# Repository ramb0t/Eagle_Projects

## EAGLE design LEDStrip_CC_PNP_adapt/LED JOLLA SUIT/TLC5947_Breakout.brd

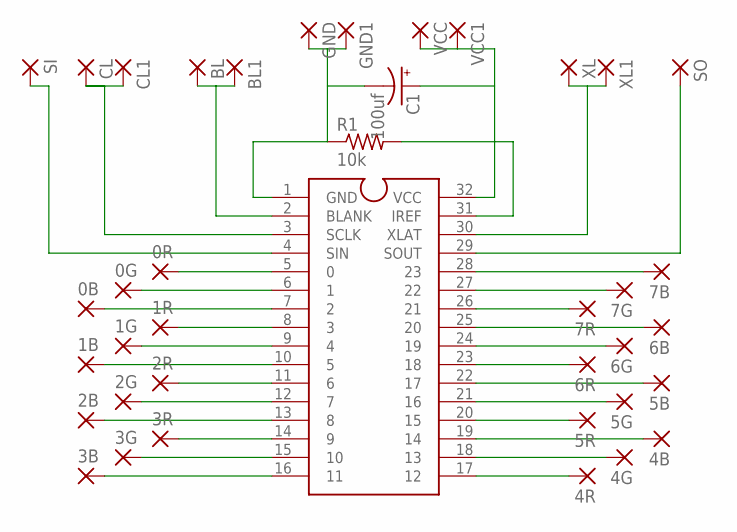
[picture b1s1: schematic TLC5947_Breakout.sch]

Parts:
0B, 0G, 0R, 1B, 1G, 1R, 2B, 2G, 2R, 3B, 3G, 3R, 4B, 4G, 4R, 5B, 5G, 5R, 6B, 6G, 6R, 7B, 7G, 7R: SMD2; SMD1,27-2,54
BL, BL1: SMD2; SMD1,27-2,54
C1: 100uf; E2,5-6
CL, CL1: SMD2; SMD1,27-2,54
GND, GND1: SMD2; SMD1,27-2,54
R1: 10k; 0207/10
SI: SMD2; SMD1,27-2,54
SO: SMD2; SMD1,27-2,54
U$1: TLC5947DAC; DAP38
VCC, VCC1: SMD2; SMD1,27-2,54
XL, XL1: SMD2; SMD1,27-2,54

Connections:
GND: C1.-, GND.1, GND1.1, R1.1, U$1.1 (GND)
unnamed: R1.2, U$1.31 (IREF)
unnamed: U$1.30 (XLAT), XL.1, XL1.1
unnamed: 0R.1, U$1.5 (0)
unnamed: 0G.1, U$1.6 (1)
unnamed: 0B.1, U$1.7 (2)
unnamed: 1R.1, U$1.8 (3)
unnamed: 1G.1, U$1.9 (4)
unnamed: 1B.1, U$1.10 (5)
unnamed: 2R.1, U$1.11 (6)
unnamed: 2G.1, U$1.12 (7)
unnamed: 2B.1, U$1.13 (8)
unnamed: 3R.1, U$1.14 (9)
unnamed: 3G.1, U$1.15 (10)
unnamed: 3B.1, U$1.16 (11)
unnamed: 4R.1, U$1.17 (12)
unnamed: 4G.1, U$1.18 (13)
unnamed: 4B.1, U$1.19 (14)
unnamed: 5R.1, U$1.20 (15)
unnamed: 5G.1, U$1.21 (16)
unnamed: 5B.1, U$1.22 (17)
unnamed: 6R.1, U$1.23 (18)
unnamed: 6G.1, U$1.24 (19)
unnamed: 6B.1, U$1.25 (20)
unnamed: 7R.1, U$1.26 (21)
unnamed: 7G.1, U$1.27 (22)
unnamed: 7B.1, U$1.28 (23)
unnamed: SI.1, U$1.4 (SIN)
unnamed: SO.1, U$1.29 (SOUT)
unnamed: CL.1, CL1.1, U$1.3 (SCLK)
unnamed: BL.1, BL1.1, U$1.2 (BLANK)
VCC: C1.+, U$1.32 (VCC), VCC.1, VCC1.1

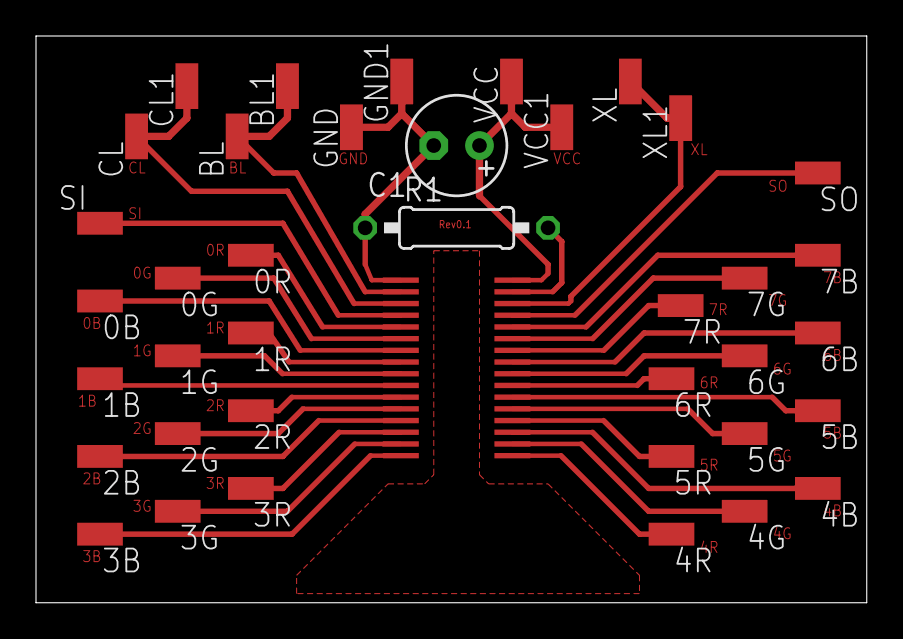
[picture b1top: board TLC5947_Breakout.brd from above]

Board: 2 copper layers, 46.2 x 31.5 mm, 39 parts (0 on the bottom side), 32 nets.

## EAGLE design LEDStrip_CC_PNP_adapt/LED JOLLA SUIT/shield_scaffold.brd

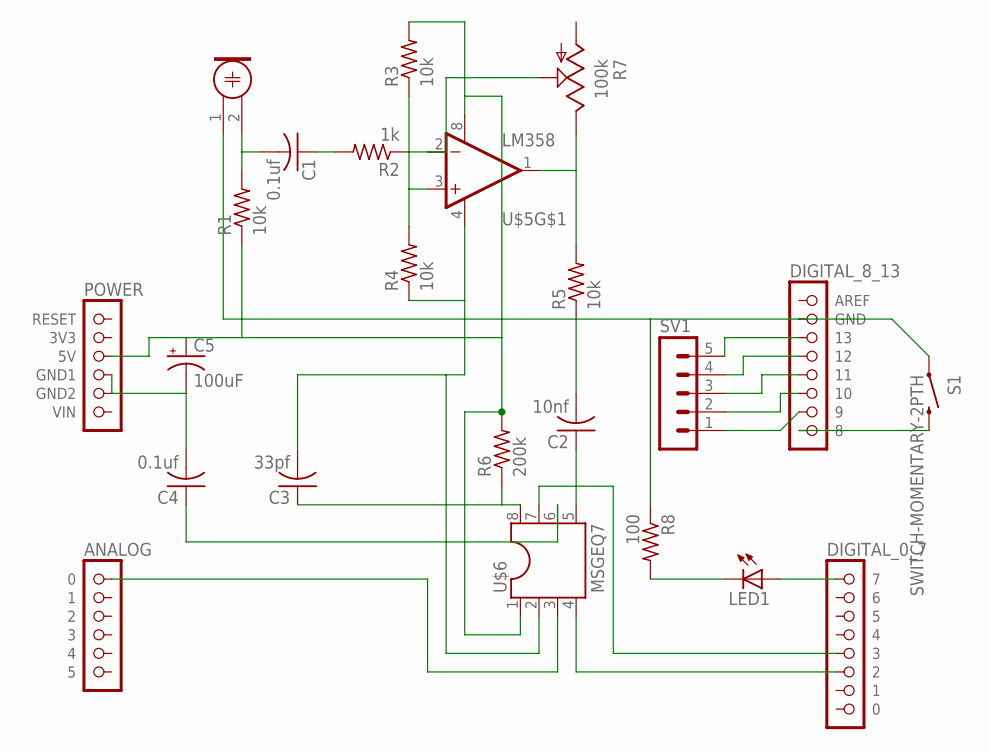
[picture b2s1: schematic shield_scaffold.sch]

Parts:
C1, C4: 0.1uf; C050-030X075
C2: 10nf; C050-030X075
C3: 33pf; C050-030X075
C5: 100uF; E3,5-8
LED1: LED3MM
M1: ELECTRET_MICROPHON-F6050AP; F6050AP
R1, R3, R4, R5: 10k; 0207/10
R2: 1k; 0207/10
R6: 200k; 0207/10
R7: 100k; PT-10
R8: 100; 0207/10
S1: SWITCH-MOMENTARY-2PTH; TACTILE-PTH
SV1: MA05-1
U$1: POWER; 1X06
U$2: ANALOG; 1X06
U$3: DIGITAL_0_7; 1X08
U$4: DIGITAL_8_13; 1X08
U$5: LM358; DIP08
U$6: MSGEQ7; SOCKET-08

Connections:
GND: C3.2, M1.1, R4.1, R8.1, S1.1, U$4.2 (GND), U$5.4 (V-), U$6.2
unnamed: C1.2, M1.2, R1.2
unnamed: C1.1, R2.2
unnamed: C4.1, U$6.6
unnamed: R2.1, R7.S, U$5.2 (-IN)
unnamed: S1.3 (2), U$4.8
unnamed: R3.1, R4.2, U$5.3 (+IN)
unnamed: R5.2, R7.E, U$5.1 (OUT)
unnamed: C2.2, R5.1
unnamed: C2.1, U$6.5
unnamed: LED1.A, U$3.1 (7)
unnamed: SV1.5, U$4.3 (13)
unnamed: U$2.1 (0), U$6.3
unnamed: U$3.6 (2), U$6.4
unnamed: C3.1, R6.1, U$6.8
unnamed: U$3.5 (3), U$6.7
unnamed: SV1.4, U$4.4 (12)
unnamed: SV1.3, U$4.5 (11)
unnamed: SV1.2, U$4.6 (10)
unnamed: SV1.1, U$4.7 (9)
unnamed: LED1.K (C), R8.2
unnamed: C4.2, C5.-, U$1.4 (GND1), U$1.5 (GND2)
unnamed: C5.+, R1.1, R3.2, R6.2, U$1.3 (5V), U$5.8 (V+), U$6.1

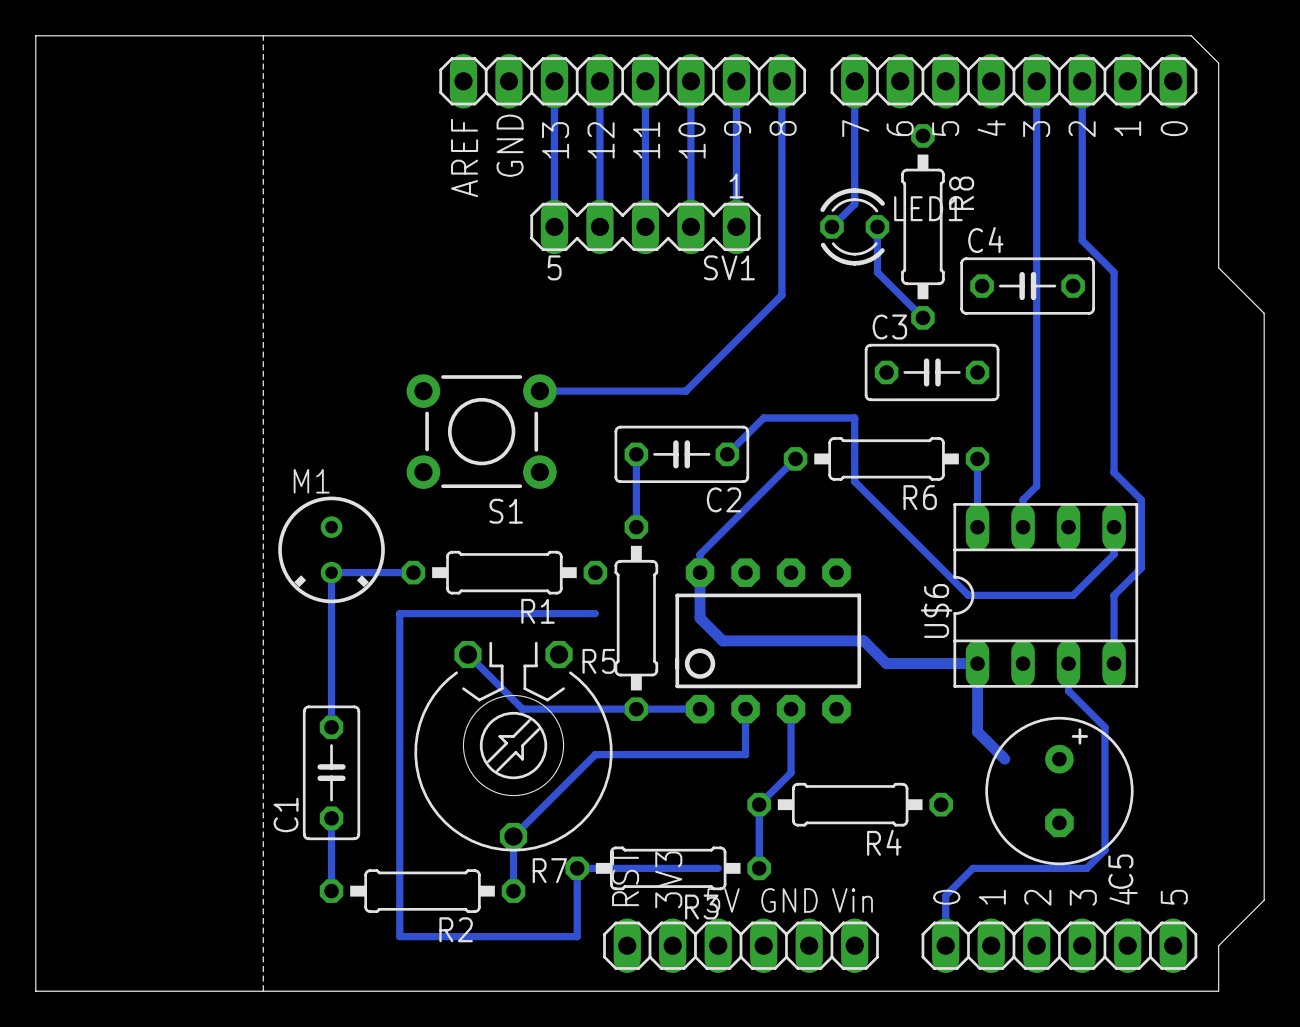
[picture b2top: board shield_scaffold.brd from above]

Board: 2 copper layers, 68.6 x 53.3 mm, 23 parts (0 on the bottom side), 23 nets.

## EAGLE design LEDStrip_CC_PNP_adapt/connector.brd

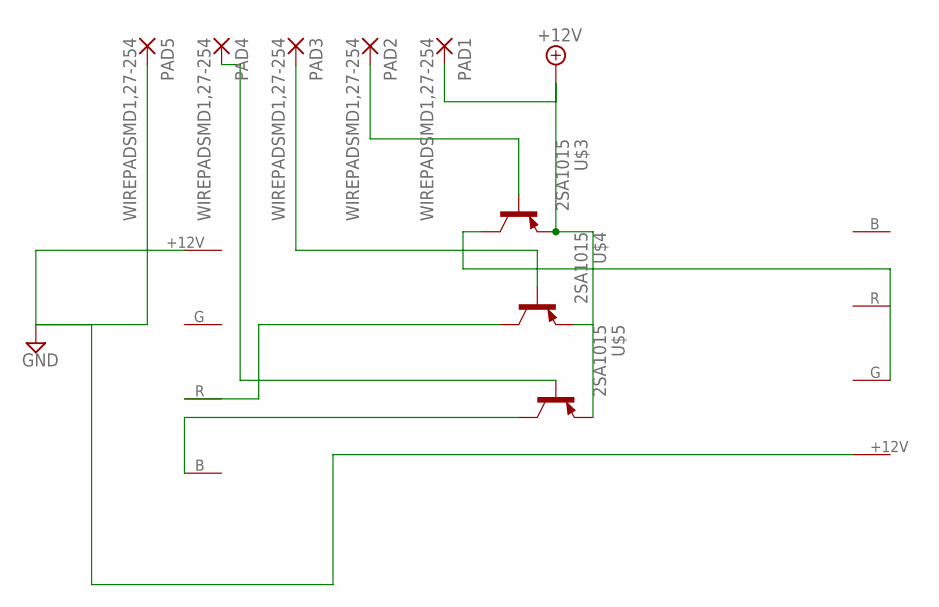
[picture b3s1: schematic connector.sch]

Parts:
PAD1, PAD2, PAD3, PAD4, PAD5: WIREPADSMD1,27-254; SMD1,27-2,54
U$1, U$2: LED_STRIP_SOLDER_PAD; STRIP
U$3, U$4, U$5: 2SA1015; TO92-EBC

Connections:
+12V: PAD1.1, U$3.E, U$4.E, U$5.E
GND: PAD5.1, U$2.+12V
unnamed: U$2.B, U$5.C
unnamed: U$2.R, U$4.C
unnamed: U$1.G, U$3.C
unnamed: PAD2.1, U$3.B
unnamed: PAD3.1, U$4.B
unnamed: PAD4.1, U$5.B

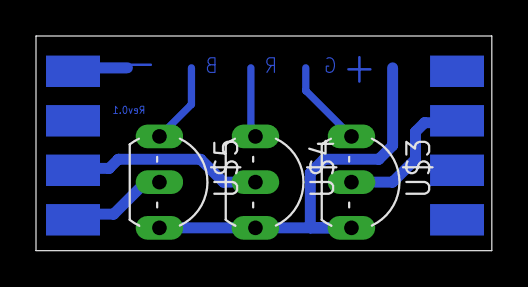
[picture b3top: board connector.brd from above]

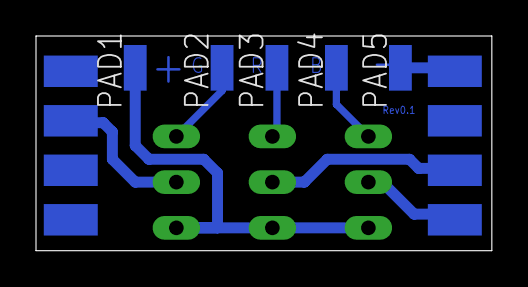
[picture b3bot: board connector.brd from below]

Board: 2 copper layers, 25.3 x 11.9 mm, 10 parts (7 on the bottom side), 8 nets.

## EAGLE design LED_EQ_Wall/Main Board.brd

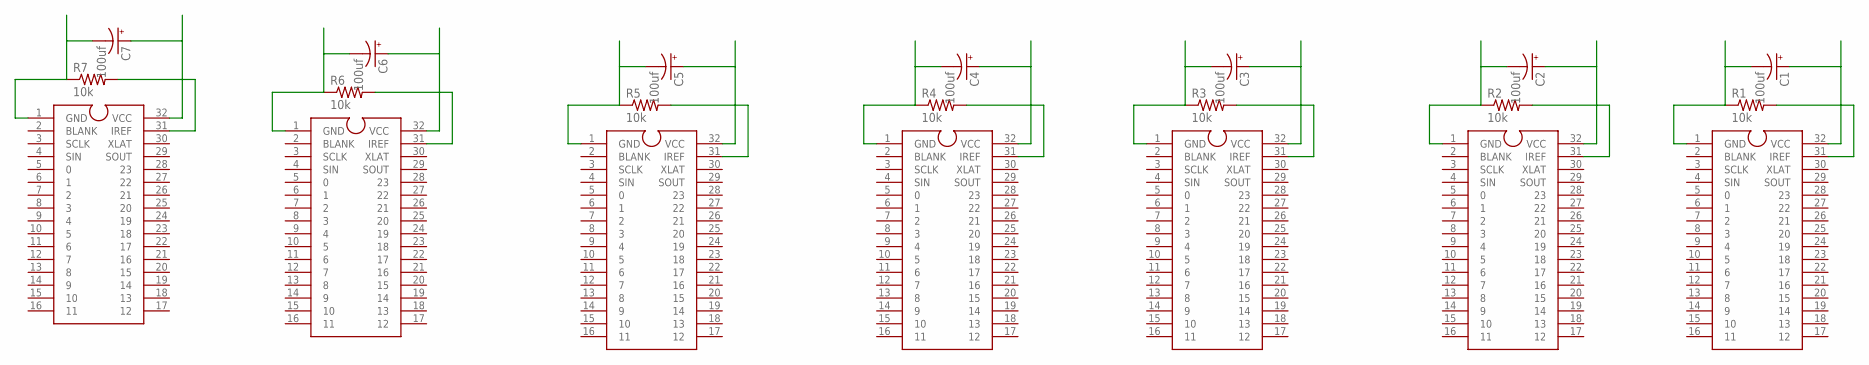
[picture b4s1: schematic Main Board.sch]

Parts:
C1, C2, C3, C4, C5, C6, C7: 100uf; E2,5-6
R1, R2, R3, R4, R5, R6, R7: 10k; 0207/10
U$1, U$2, U$3, U$4, U$5, U$6, U$7: TLC5947DAC; DAP38

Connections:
GND: C1.-, R1.1, U$1.1 (GND)
GND1: C2.-, R2.1, U$2.1 (GND)
GND2: C3.-, R3.1, U$3.1 (GND)
GND3: C4.-, R4.1, U$4.1 (GND)
GND4: C5.-, R5.1, U$5.1 (GND)
GND5: C6.-, R6.1, U$6.1 (GND)
GND6: C7.-, R7.1, U$7.1 (GND)
unnamed: R1.2, U$1.31 (IREF)
unnamed: R2.2, U$2.31 (IREF)
unnamed: R3.2, U$3.31 (IREF)
unnamed: R4.2, U$4.31 (IREF)
unnamed: R5.2, U$5.31 (IREF)
unnamed: R6.2, U$6.31 (IREF)
unnamed: R7.2, U$7.31 (IREF)
VCC: C1.+, U$1.32 (VCC)
VCC1: C2.+, U$2.32 (VCC)
VCC2: C3.+, U$3.32 (VCC)
VCC3: C4.+, U$4.32 (VCC)
VCC4: C5.+, U$5.32 (VCC)
VCC5: C6.+, U$6.32 (VCC)
VCC6: C7.+, U$7.32 (VCC)

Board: 2 copper layers, 21 parts (0 on the bottom side), 21 nets, no tracks yet.

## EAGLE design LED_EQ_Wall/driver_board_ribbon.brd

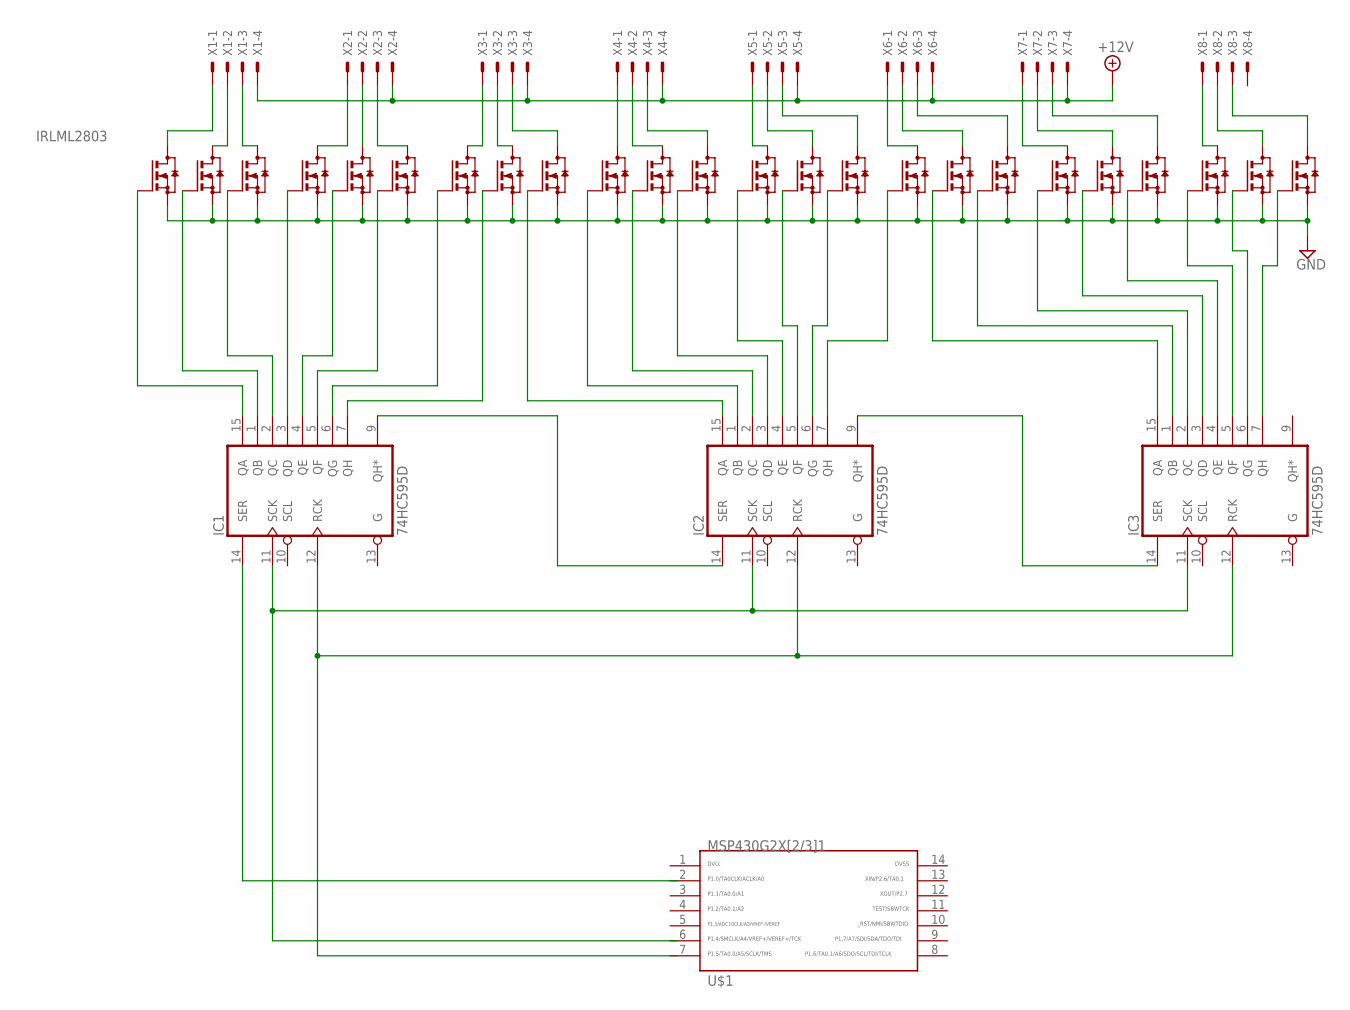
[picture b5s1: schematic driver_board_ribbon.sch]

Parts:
IC1, IC2, IC3: 74HC595D; SO16
U$1: G2X[2/3]1---PW14; PW14
U$3, U$4, U$5, U$6, U$7, U$8, U$9, U$10, U$11, U$12, U$13, U$14, U$15, U$16, U$17, U$18, U$19, U$20, U$21, U$22, U$23, U$24, U$25, U$26: IRLML2803; SOT23
X1, X2, X3, X4, X5, X6, X7, X8: KK-156-4

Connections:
+12V: X1.4, X2.4, X3.4, X4.4, X5.4, X6.4, X7.4
GND: IC1.8 (GND), IC2.8 (GND), IC3.8 (GND), U$3.2 (S), U$4.2 (S), U$5.2 (S), U$6.2 (S), U$7.2 (S), U$8.2 (S), U$9.2 (S), U$10.2 (S), U$11.2 (S), U$12.2 (S), U$13.2 (S), U$14.2 (S), U$15.2 (S), U$16.2 (S), U$17.2 (S), U$18.2 (S), U$19.2 (S), U$20.2 (S), U$21.2 (S), U$22.2 (S), U$23.2 (S), U$24.2 (S), U$25.2 (S), U$26.2 (S)
unnamed: IC1.9 (QH*), IC2.14 (SER)
unnamed: IC2.9 (QH*), IC3.14 (SER)
unnamed: IC1.11 (SCK), IC2.11 (SCK), IC3.11 (SCK)
unnamed: IC1.12 (RCK), IC2.12 (RCK), IC3.12 (RCK)
unnamed: U$3.3 (D), X1.1
unnamed: U$4.3 (D), X1.2
unnamed: U$5.3 (D), X1.3
unnamed: U$6.3 (D), X2.1
unnamed: U$7.3 (D), X2.2
unnamed: U$8.3 (D), X2.3
unnamed: U$9.3 (D), X3.1
unnamed: U$10.3 (D), X3.2
unnamed: U$11.3 (D), X3.3
unnamed: U$12.3 (D), X4.1
unnamed: U$13.3 (D), X4.2
unnamed: U$14.3 (D), X4.3
unnamed: U$15.3 (D), X5.1
unnamed: U$16.3 (D), X5.2
unnamed: U$17.3 (D), X5.3
unnamed: U$18.3 (D), X6.1
unnamed: U$19.3 (D), X6.2
unnamed: U$20.3 (D), X6.3
unnamed: U$21.3 (D), X7.1
unnamed: U$22.3 (D), X7.2
unnamed: U$23.3 (D), X7.3
unnamed: U$24.3 (D), X8.1
unnamed: U$25.3 (D), X8.2
unnamed: U$26.3 (D), X8.3
unnamed: IC1.7 (QH), U$10.1 (G)
unnamed: IC1.6 (QG), U$9.1 (G)
unnamed: IC1.5 (QF), U$8.1 (G)
unnamed: IC1.4 (QE), U$7.1 (G)
unnamed: IC1.3 (QD), U$6.1 (G)
unnamed: IC1.2 (QC), U$5.1 (G)
unnamed: IC1.1 (QB), U$4.1 (G)
unnamed: IC1.15 (QA), U$3.1 (G)
unnamed: IC2.15 (QA), U$11.1 (G)
unnamed: IC2.1 (QB), U$12.1 (G)
unnamed: IC2.2 (QC), U$13.1 (G)
unnamed: IC2.3 (QD), U$14.1 (G)
unnamed: IC2.4 (QE), U$15.1 (G)
unnamed: IC2.5 (QF), U$16.1 (G)
unnamed: IC2.6 (QG), U$17.1 (G)
unnamed: IC2.7 (QH), U$18.1 (G)
unnamed: IC3.15 (QA), U$19.1 (G)
unnamed: IC3.1 (QB), U$20.1 (G)
unnamed: IC3.2 (QC), U$21.1 (G)
unnamed: IC3.3 (QD), U$22.1 (G)
unnamed: IC3.4 (QE), U$23.1 (G)
unnamed: IC3.5 (QF), U$24.1 (G)
unnamed: IC3.6 (QG), U$25.1 (G)
unnamed: IC3.7 (QH), U$26.1 (G)
VCC: IC1.16 (VCC), IC2.16 (VCC), IC3.16 (VCC)

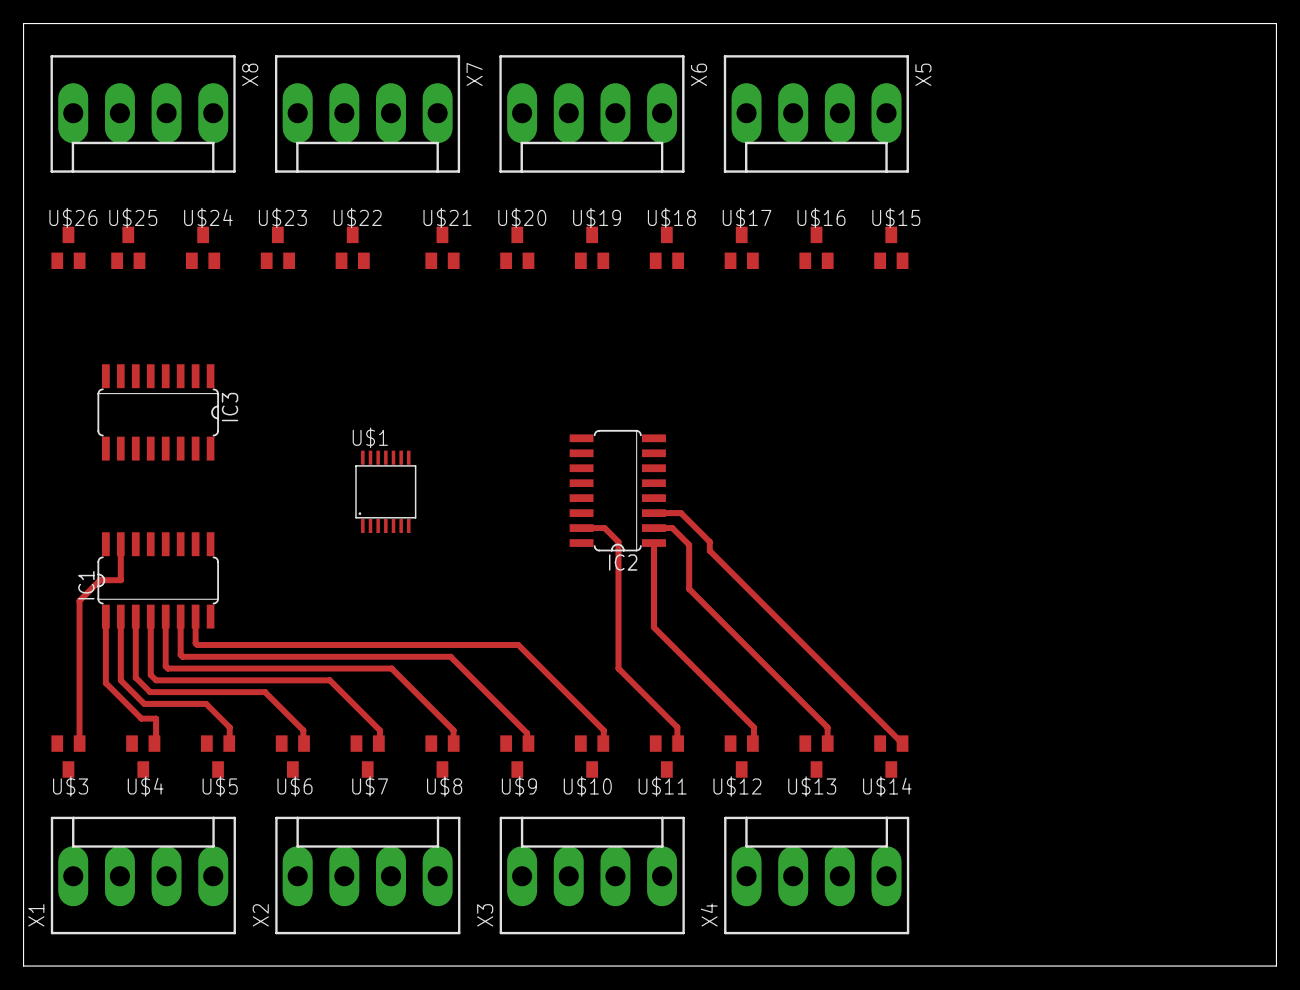
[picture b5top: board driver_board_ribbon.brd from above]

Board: 2 copper layers, 106.3 x 80.0 mm, 36 parts (0 on the bottom side), 55 nets.

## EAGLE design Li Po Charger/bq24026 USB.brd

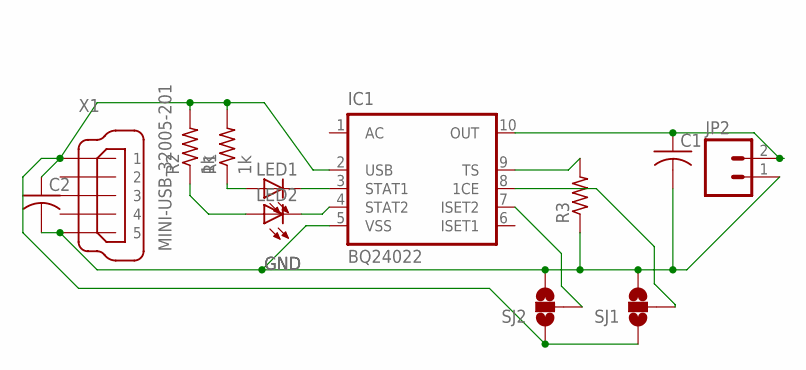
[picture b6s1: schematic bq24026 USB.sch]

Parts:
C1, C2: C-USC0805K; C0805K
IC1: BQ24022; DRC-S-PVSON-N10
JP2: M02; 1X02_LONGPADS
LED1, LED2: LEDCHIPLED_0805; CHIPLED_0805
R1, R2: 1k; M0805
R3: R-US_M1206; M1206
SJ1, SJ2: SOLDERJUMPER_2WAYS; SJ_3
X1: MINI-USB-32005-201; 32005-201

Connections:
GND: C1.2, C2.2, IC1.5 (VSS), JP2.1, R3.1, SJ1.3, SJ2.3, X1.5
unnamed: IC1.9 (TS), R3.2
unnamed: C2.1, IC1.2 (USB), R1.2, R2.2, X1.1
unnamed: LED1.A, R1.1
unnamed: LED2.A, R2.1
unnamed: IC1.3 (STAT1), LED1.C
unnamed: IC1.4 (STAT2), LED2.C
unnamed: IC1.7 (ISET2), SJ2.2
unnamed: C1.1, IC1.10 (OUT), JP2.2
unnamed: IC1.8 (1CE), SJ1.2
unnamed: SJ1.1, SJ2.1

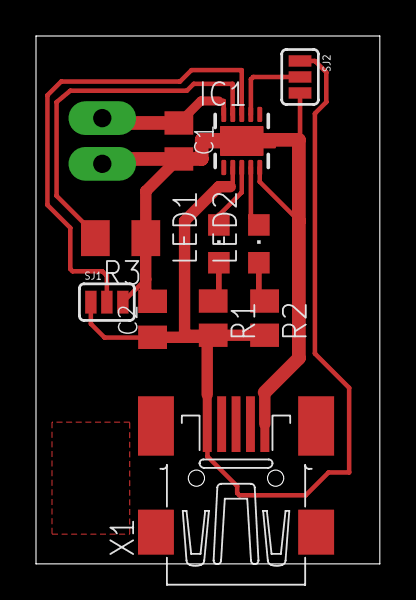
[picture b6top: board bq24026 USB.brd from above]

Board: 2 copper layers, 19.1 x 29.3 mm, 12 parts (0 on the bottom side), 11 nets.

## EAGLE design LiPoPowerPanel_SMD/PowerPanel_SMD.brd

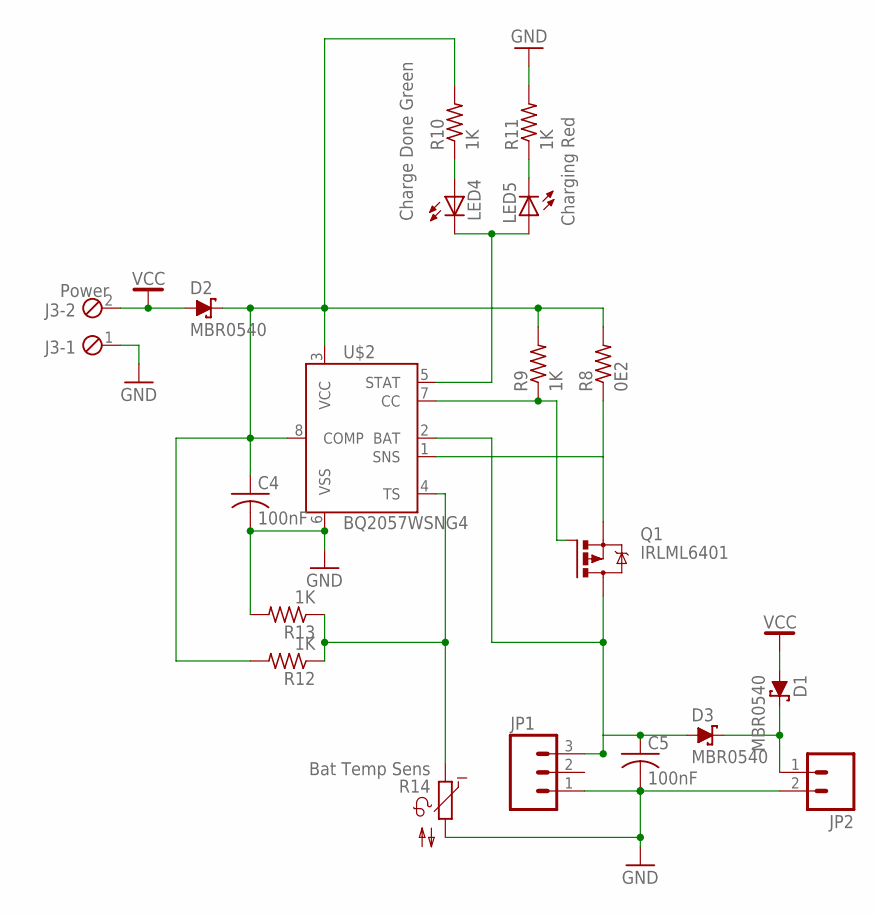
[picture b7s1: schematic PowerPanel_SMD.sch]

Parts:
C4, C5: 100nF; C0805K
D1, D2, D3: MBR0540; SOD123
J3: Power; 796689-2
JP1: M03LONGPADS; 1X03_LONGPADS
JP2: M02PTH3; 1X02_LONGPADS
LED4: Charge Done Green; CHIPLED_0805
LED5: Charging Red; CHIPLED_0805
Q1: IRLML6401; MICRO3
R8: 0E2; M1206
R9, R10, R11, R12, R13: 1K; R0805
R14: Bat Temp Sens; P640
U$2: BQ2057WSNG4; D_R-PDSO-G8

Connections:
GND: C4.2, C5.2, J3.1, JP1.1, JP2.2, R11.2, R13.2, R14.2, U$2.6 (VSS)
unnamed: D1.C, D3.C, JP2.1
unnamed: LED4.C, LED5.A, U$2.5 (STAT)
unnamed: C5.1, D3.A, JP1.3, Q1.3 (D), U$2.2 (BAT)
unnamed: Q1.2 (S), R8.1, U$2.1 (SNS)
unnamed: Q1.1 (G), R9.1, U$2.7 (CC)
unnamed: LED5.C, R11.1
unnamed: LED4.A, R10.1
unnamed: R12.1, R13.1, R14.1, U$2.4 (TS)
unnamed: C4.1, D2.C, R8.2, R9.2, R10.2, R12.2, U$2.3 (VCC), U$2.8 (COMP)
VCC: D1.A, D2.A, J3.2

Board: 2 copper layers, 19 parts (0 on the bottom side), 11 nets, no tracks yet.

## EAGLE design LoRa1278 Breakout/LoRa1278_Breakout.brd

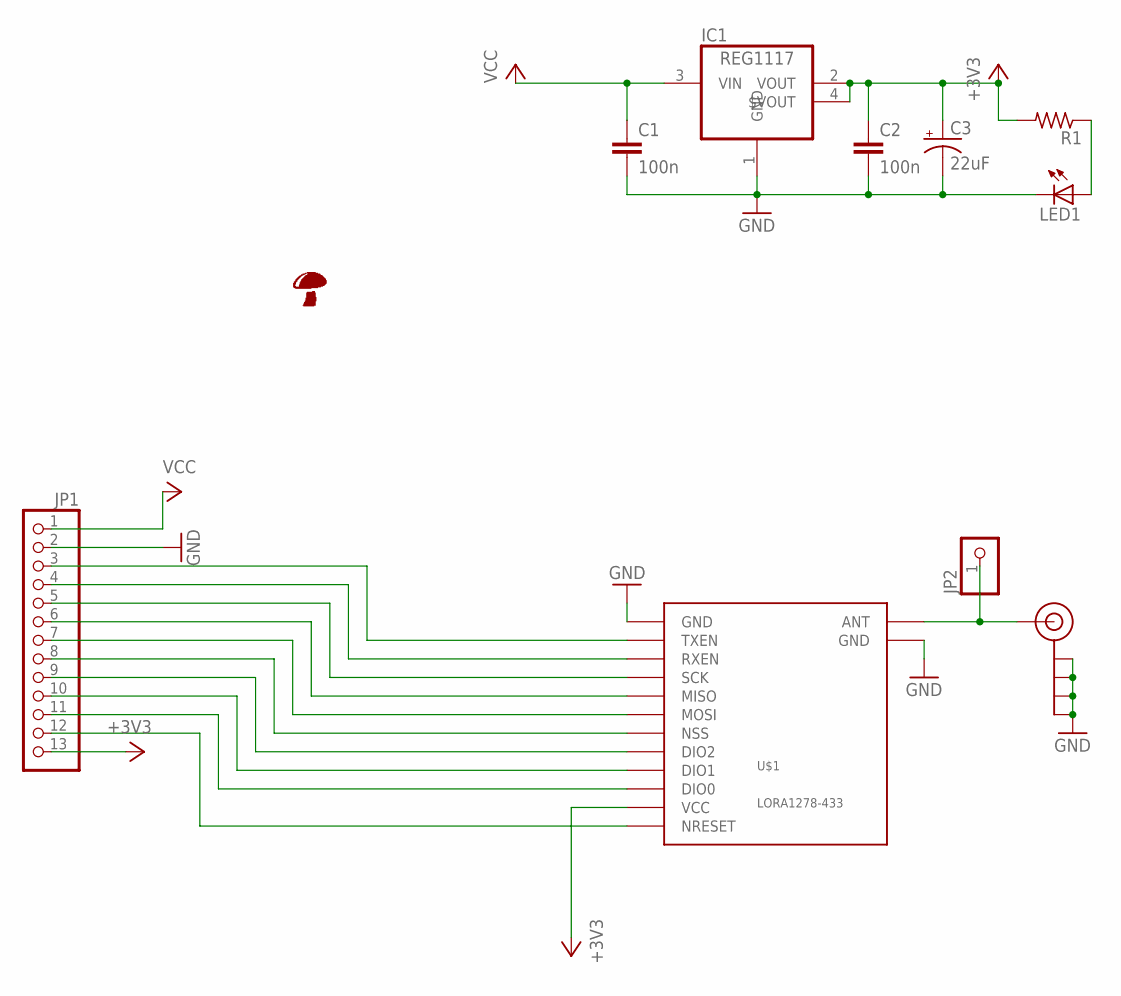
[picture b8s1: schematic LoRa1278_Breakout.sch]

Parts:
C1, C2: 100n; C0805
C3: 22uF; PANASONIC_C
IC1: REG1117; SOT223
J$1: SMA_EDGE; SMA-EDGE
JP1: PINHD-1X13; 1X13
JP2: PINHD-1X1; 1X01
LED1: LEDCHIP-LED0805; CHIP-LED0805
R1: R-US_R0805; R0805
U$1: LORA1278-433; LORA1278
U$2: SHROOM5MM; SHROOM

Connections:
+3V3: C2.1, C3.+, IC1.2 (VOUT), IC1.4 ($VOUT), JP1.13, R1.2, U$1.P$11 (VCC)
GND: C1.2, C2.2, C3.-, IC1.1 (GND), J$1.GND@0 (GND), J$1.GND@1 (GND), J$1.GND@2 (GND), J$1.GND@3 (GND), JP1.2, LED1.C, U$1.P$1 (GND), U$1.P$14 (GND)
unnamed: JP1.3, U$1.P$2 (TXEN)
unnamed: JP1.4, U$1.P$3 (RXEN)
unnamed: JP1.5, U$1.P$4 (SCK)
unnamed: JP1.6, U$1.P$5 (MISO)
unnamed: JP1.7, U$1.P$6 (MOSI)
unnamed: JP1.8, U$1.P$7 (NSS)
unnamed: JP1.9, U$1.P$8 (DIO2)
unnamed: JP1.10, U$1.P$9 (DIO1)
unnamed: JP1.11, U$1.P$10 (DIO0)
unnamed: JP1.12, U$1.P$12 (NRESET)
unnamed: J$1.SIG (SIGNAL), JP2.1, U$1.P$13 (ANT)
unnamed: LED1.A, R1.1
VCC: C1.1, IC1.3 (VIN), JP1.1

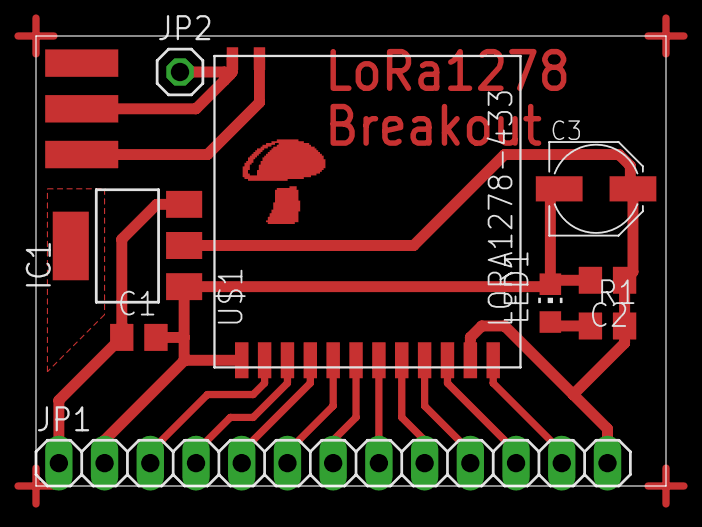
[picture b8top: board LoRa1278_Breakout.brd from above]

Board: 2 copper layers, 35.0 x 25.0 mm, 11 parts (0 on the bottom side), 15 nets.

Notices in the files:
parts and their libraries:
SparkFun: Licensing: CC v3.0 Share-Alike You are welcome to use this library for commercial purposes.
con-tyco: Copyright (C) 2009, Bob Starr
supply0: Copyright (C) 2007, Bob Starr
